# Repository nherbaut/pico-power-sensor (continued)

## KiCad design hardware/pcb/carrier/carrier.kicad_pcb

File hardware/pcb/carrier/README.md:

# PicoPower carrier — rev A engineering draft

This board sockets a Pico 2 W, provides five programmable green LEDs and a microSD slot, and carries the INA229 power monitor, fed from the interposer through a four-pin JST-XH sense connector. A five-pin JST-XH connector joins the carrier to the buffered Pi interposer. The carrier has its own USB-powered supply; instrument loads remain outside DUT energy measurements.

## Electrical schematic

This is the current KiCad schematic, including the five LED branches, INA229 and sense connector, UART connector, SPI1 microSD slot and dedicated card regulator. Matching net names are electrical connections. Click the PNG to read individual pin numbers and component values.

[Open full-size schematic PNG](schematic.png) · [Download schematic PDF](schematic.pdf).

## Front PCB layout

The sense connector and INA229 sit in a strip at the left edge, the Pico sockets in the middle, five LEDs along the right edge, and the hinged card socket in the lower-left. The UART JST-XH connector is above the microSD area. Four mounting holes provide support on a shared bench base.

[Open full-size PCB PNG](layout-front.png) · [Original front SVG](layout-front.svg).

## Review files

- [KiCad project](carrier.kicad_pro), [schematic](carrier.kicad_sch) and [routed PCB](carrier.kicad_pcb).
- [Schematic PDF](schematic.pdf), [front copper](layout-front.svg) and [back copper](layout-back.svg), viewed from above.
- [Mounting drawing](mounting.svg), [pinout](pinout.csv), [board BOM](board-bom.csv) and [circuit source](circuit.json).
- [Portable review archive](carrier-review.zip), including the local symbol and footprint libraries.
- [ERC](checks/erc.rpt), [DRC and schematic parity](checks/drc.rpt), and [source/PCB checks](checks/source-check.json).
- [PNG export provenance](images.json): source CAD hashes and image dimensions.

Open `carrier.kicad_pro` in KiCad 9. The schematic uses named nets: matching names are electrical connections. LED polarity is explicitly labelled A/K. `J_PICO` uses a combined socketed-Pico footprint; fit two 1x20 female strips at 17.78 mm row separation, with a compatible headered Pico. Its module/header height requires physical review.

`make carrier-build` deliberately overwrites carrier CAD and routes it again. Save interactive edits before using it. `make carrier-check`, `make carrier-erc` and `make carrier-drc` check the source/PCB mapping and native CAD. `make carrier-export` requires all checks to pass before exporting the review archive. Existing interposer build targets remain independent. These commands need KiCad 9, the distribution Python `pcbnew` module and NumPy.

## Electrical and mechanical choices

LED1-LED5 use GP27, GP26, GP22, GP21 and GP20 (physical pins 32, 31, 29, 27, 26), each with a 1 kOhm series resistor and a 100 kOhm GPIO pull-down. High turns an LED on; low turns it off. Firmware functions and PWM remain programmable. The [LED datasheet](https://www.kingbrightusa.com/images/catalog/spec/apt2012lzgck.pdf) gives typical Vf 2.65 V at 2 mA; using this voltage gives a 0.65 mA reference estimate per LED, not a solved operating point. Actual current and brightness remain bench checks. See the [current calculations](../../../docs/pico-carrier.md).

`J_UART` is JST B5B-XH-A(LF)(SN), with pins 1-5: GND, PICO_RX, PICO_TX, PICO_MARK, PICO_3V3. A straight-through five-wire harness uses XHP-5 housings at both ends and ten SXH-001T-P0.6 contacts. Pin 5 supplies the interposer buffer from the Pico. See the [wiring procedure](../../../docs/wiring.md).

`J_SENSE` is JST B4B-XH-A(LF)(SN), pins 1-4: SENSE_PLUS, SENSE_MINUS, SENSE_VBUS, GND, joined to interposer J3 with a straight-through XHP-4 cable. `U_PM` is the INA229AIDGSR (VSSOP-10): SPI0 on GP4-GP7 (physical 6, 7, 9, 10), ALERT on GP3, 100 nF bypass `C_PM`, a 100 kOhm CS pull-up and a 10 kOhm ALERT pull-up, all to PICO_3V3. Pin numbering follows TI SLYS023A table 5-1. The footprint is the KiCad VSSOP-10 snapshot; it has not yet been compared with TI's DGS0010A land pattern. The sense pair is fanned out from the 0.5 mm pins to J_SENSE; its Kelvin routing needs review.

J_SD uses a hinged Würth 693072010801 socket on SPI1 (GP12-GP15), separate from INA229 SPI0 (GP4-GP7). Five 10 kOhm pull-ups bias CMD/DAT0-DAT3. A TLV75533PDBVR supplies SD_3V3 from Pico USB VBUS, enabled by PICO_3V3, with 4.7 uF input/output capacitors and 22 uF/100 nF near the slot. The rails are not joined. The socket has no card-detect switch; recording requires future buffered logger firmware. See the [storage and power details](../../../docs/pico-carrier.md).

The board is 78 x 54 mm, 1.6 mm FR4, with two 35 um copper layers. Four 2.7 mm NPTH mounting holes at (4,4), (74,4), (4,50), (74,50) mm have 6 mm copper keepouts. Use M2.5 nylon hardware on a shared bench base and match board height without stressing connectors. The antenna has a copper keepout on both sides; keep base material, metal hardware and cables clear of the antenna region.

## Rebuilding the board

`make carrier-build` (generate, then the grid router) does **not currently reproduce this board**. On 2026-10-14, after the INA229 change, four regeneration attempts failed inside the router with "No route for ..." on different nets, including attempts in a scratch directory and with fixed hash seeds; the cause was not identified. The saved `carrier.kicad_pcb` (routed, with ERC, DRC and parity clean) is therefore the source of truth. Edit it in KiCad or with a targeted script that starts from the routed board, and do not run `make carrier-build` over it. A known-good copy of the routed board and its `circuit.json` is kept locally in `.build/carrier-good/`, which git ignores, so commit the board before experimenting.

## Release and physical acceptance

**Engineering draft, not fabrication-ready.** Automated reports describe CAD checks only. There are no released Gerbers, procurement actions or carrier firmware. Native footprints are snapshotted locally; the Sullins socket is a custom dimensional draft. Complete component/circuit/footprint/orientation review and physical mock-up before prototype fabrication; complete assembled-board electrical tests before DUT connection. The [CSV checklist](../../release-checklist.csv), [release procedure](../../../docs/release.md) and [current review findings](../../review/README.md) record both gates, which remain blocked.

KiCad 9.0.9 reports zero ERC violations, zero DRC violations, zero unconnected pads and zero schematic parity issues. Ten carrier regression tests cover connector mappings, LED GPIOs, separate SD power and SPI1 allocation; run them with the thirteen existing interposer tests. Re-run checks after edits; do not suppress violations to obtain a release.

With instrument and DUT supplies disabled, verify connector continuity, LED polarity and separation from DUT power. After electrical review, validate independent USB power and the INA229 3.3 V supply before attaching DUT sense wiring. Exercise all five LEDs individually, together and with PWM; check reset behavior. Validate SPI device identification first: the INA229's MANUFACTURER_ID register (address 3Eh) reads 0x5449 ("TI" in ASCII) and its DEVICE_ID register (3Fh) reads 0x2291 on the datasheet revision read, where the upper twelve bits (0x229) identify the device and the low four bits are the die revision (a different revision does not by itself mean a fake). Then validate ALERT, UART and marker signals, then card write/read checks and supply stability with SD writes, Wi-Fi and all indicators active. Measure card current peaks and regulator temperature; the 500 mA regulator rating is not a board-level continuous-load guarantee. Follow the existing interposer power-off procedure. Firmware/test tooling for these bench exercises is a separate milestone.

Record actual module revisions, socket height, supply voltages, traces, equipment and results. A Linux shutdown alone is not proof that Pi 3.3 V is off. Physical acceptance remains **not performed**.

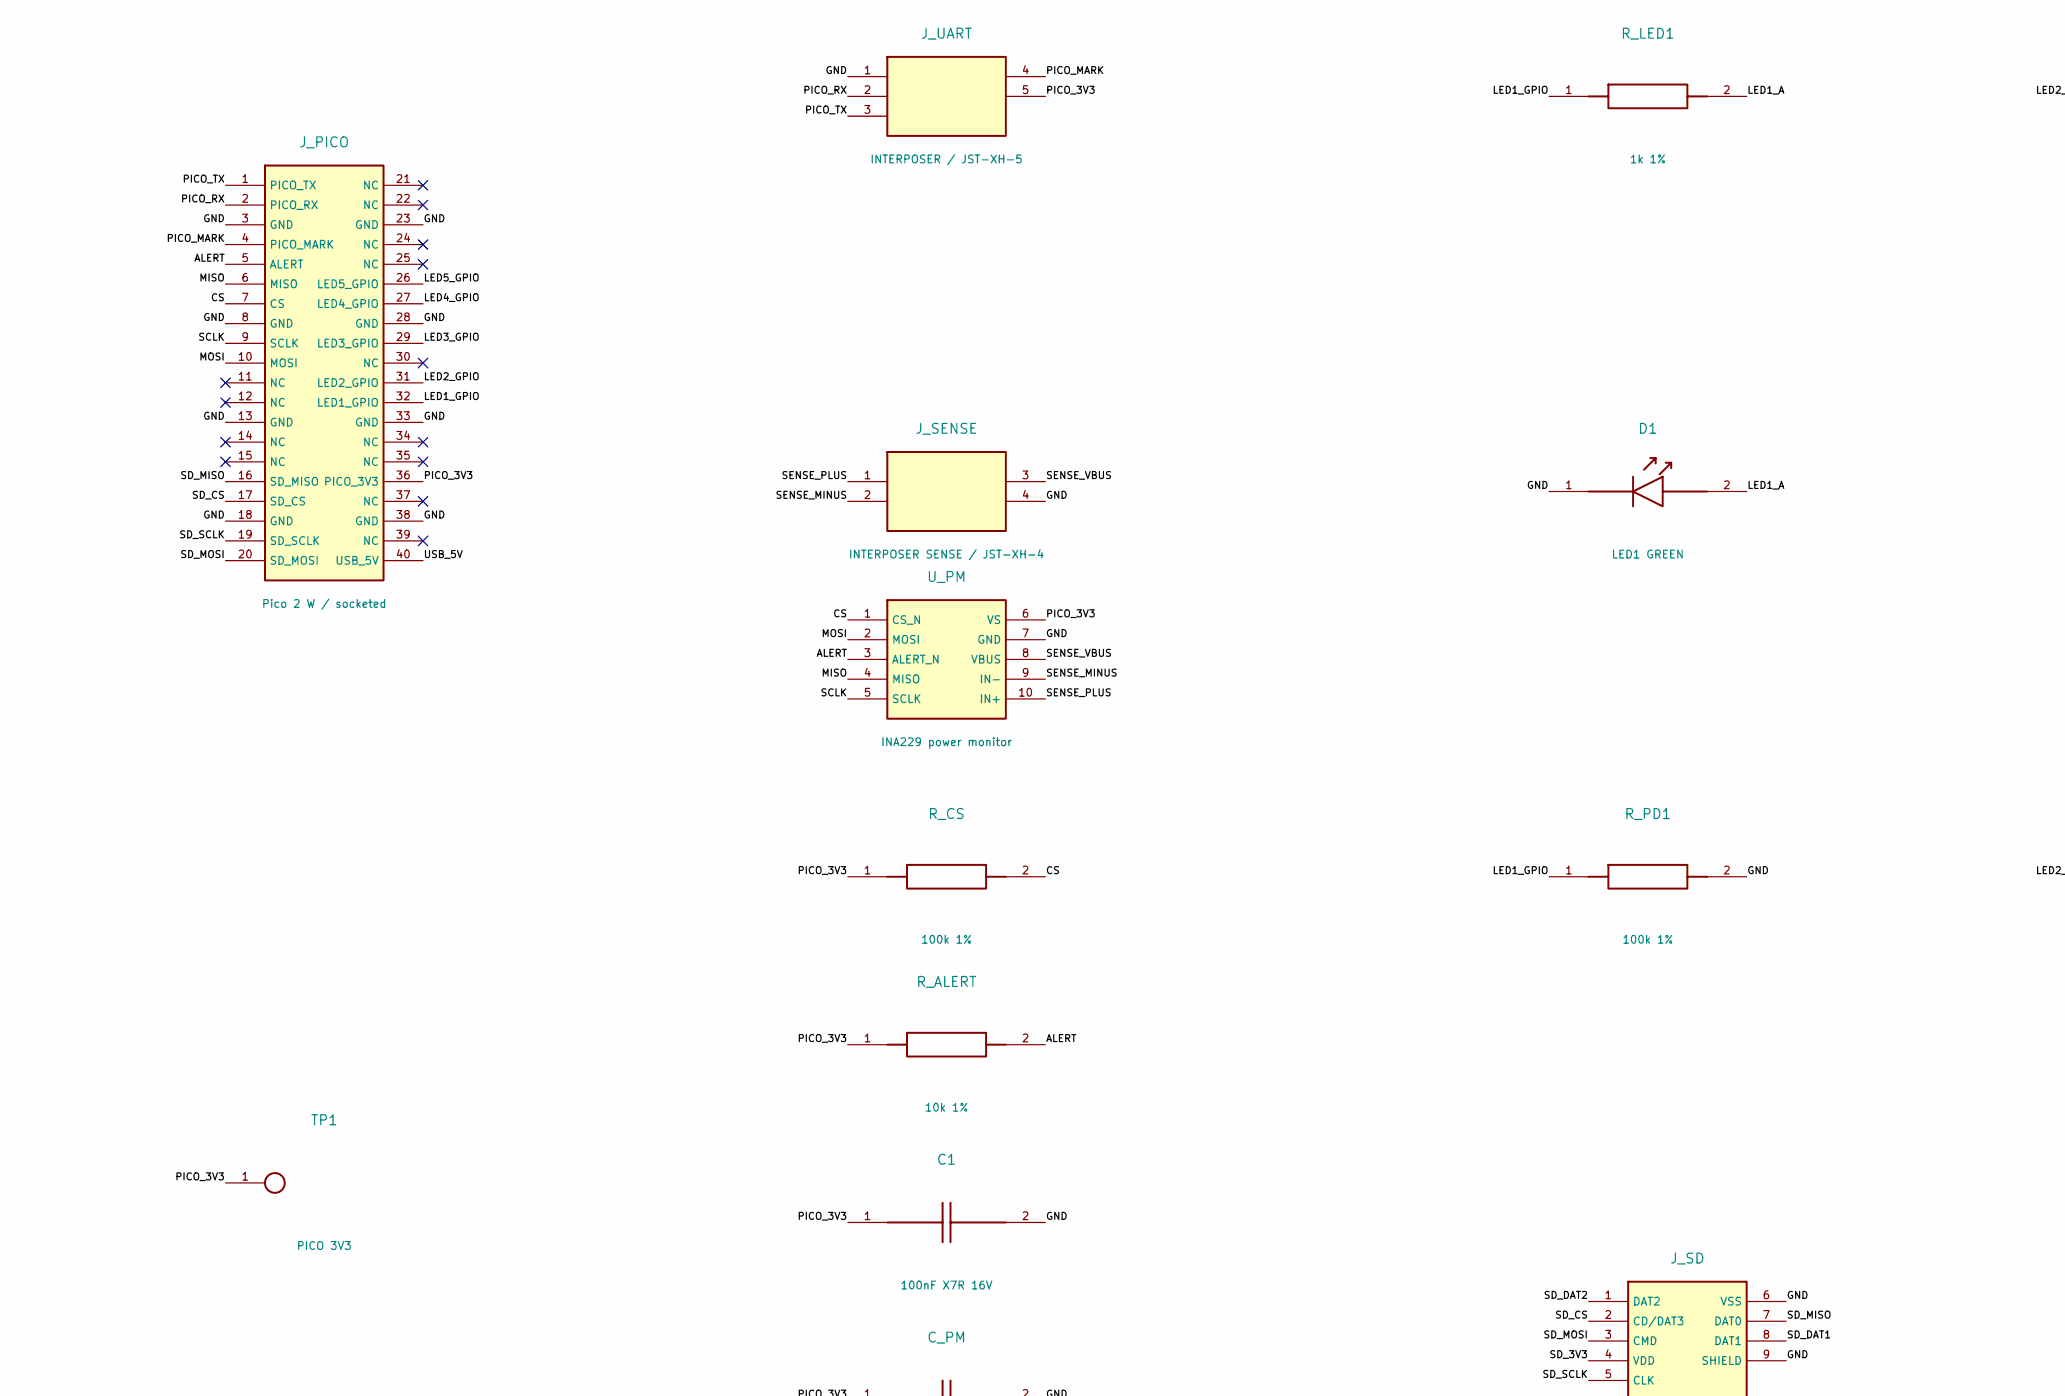
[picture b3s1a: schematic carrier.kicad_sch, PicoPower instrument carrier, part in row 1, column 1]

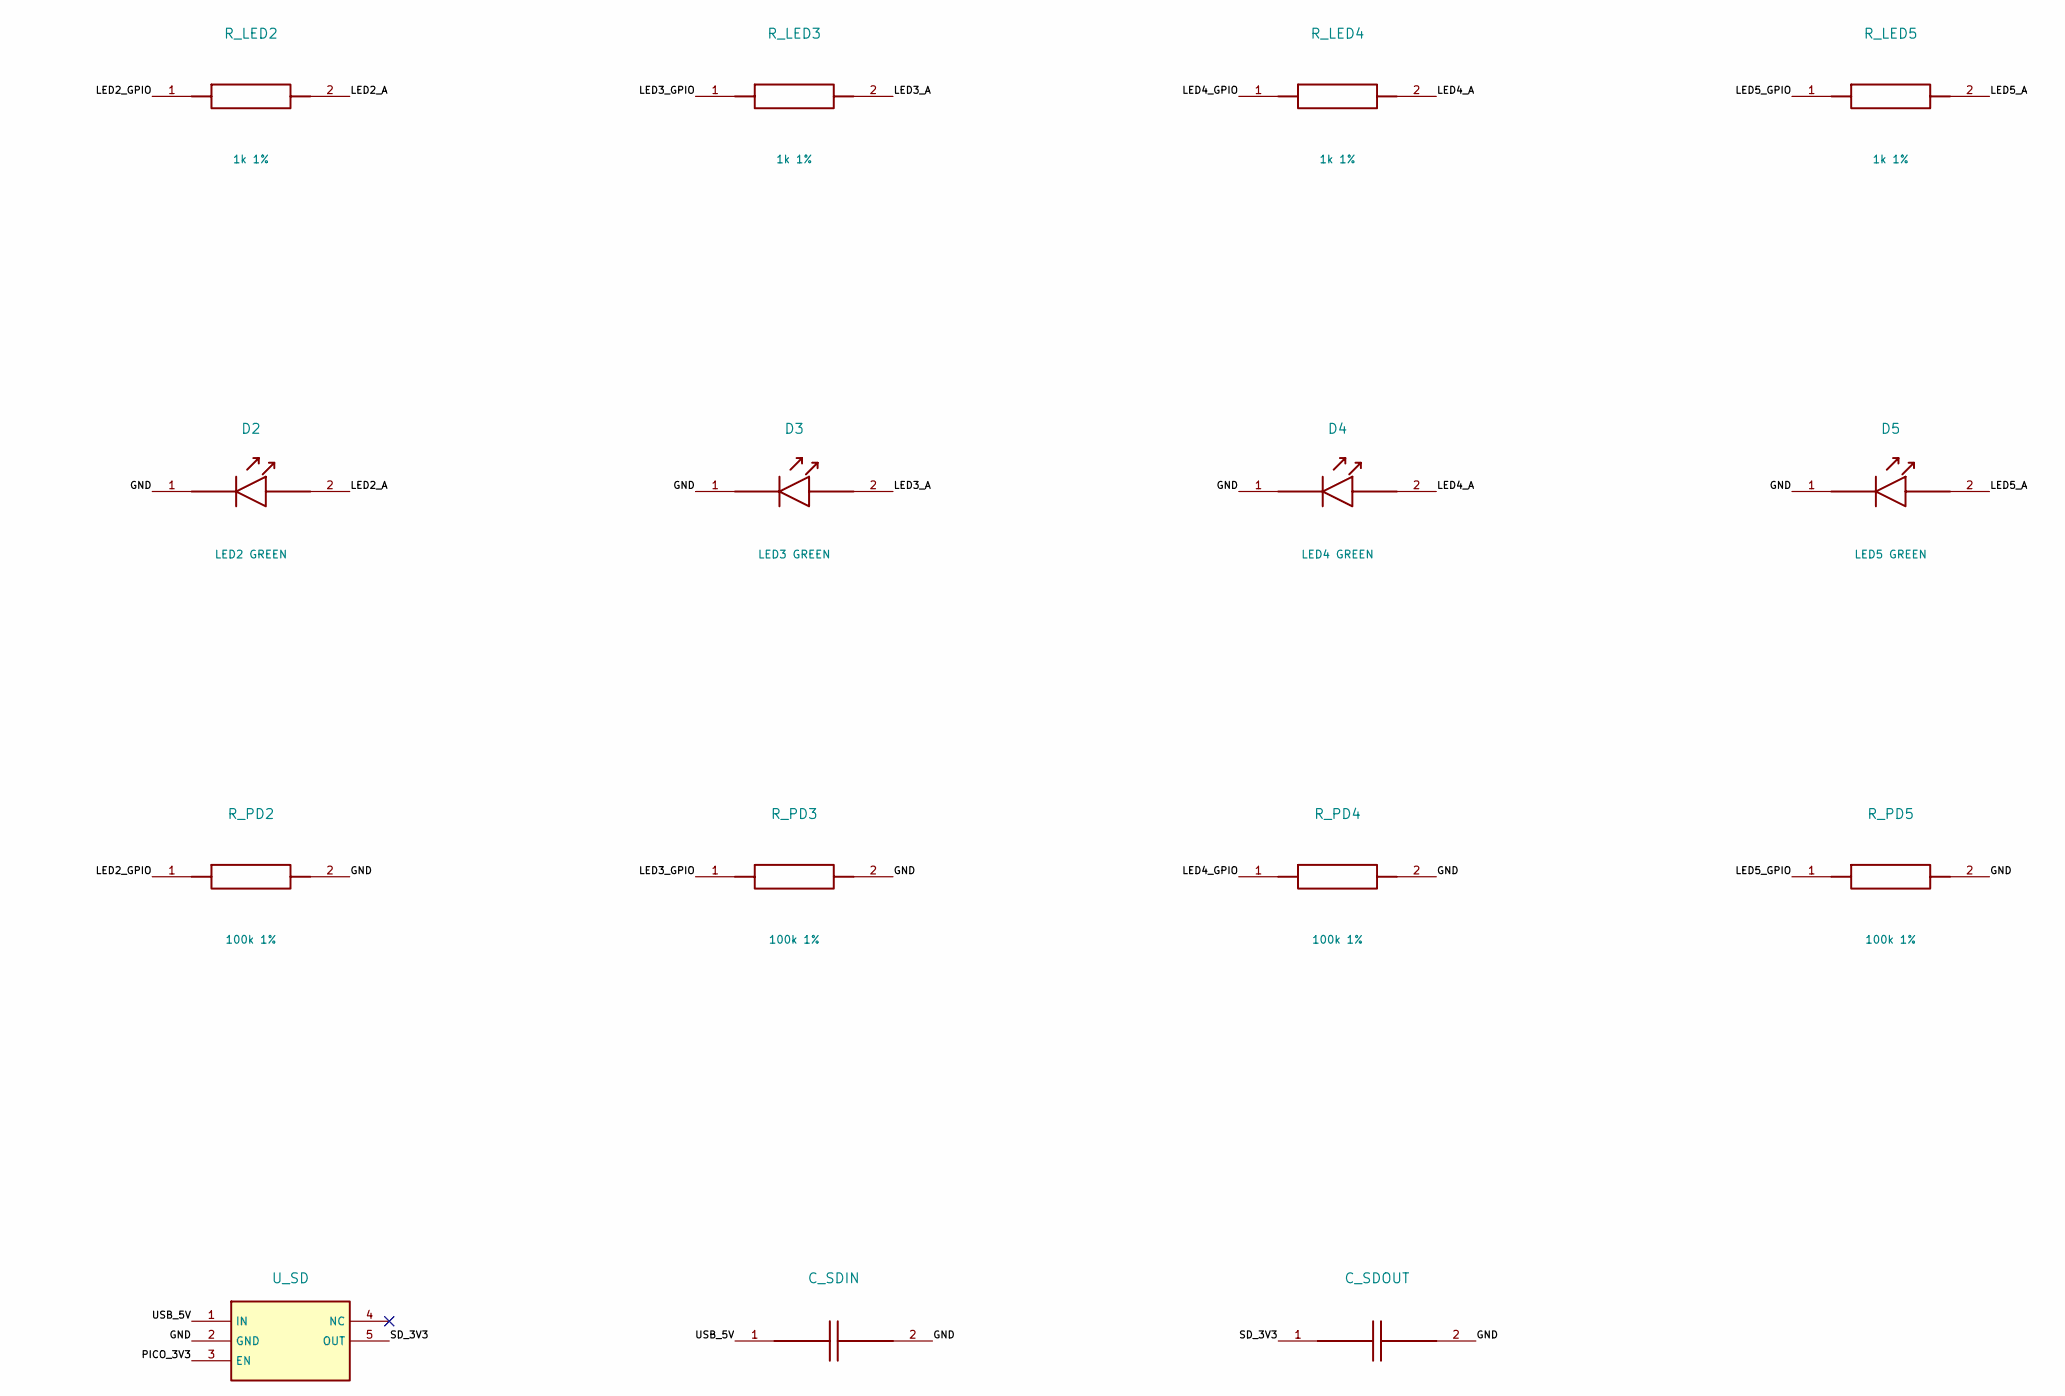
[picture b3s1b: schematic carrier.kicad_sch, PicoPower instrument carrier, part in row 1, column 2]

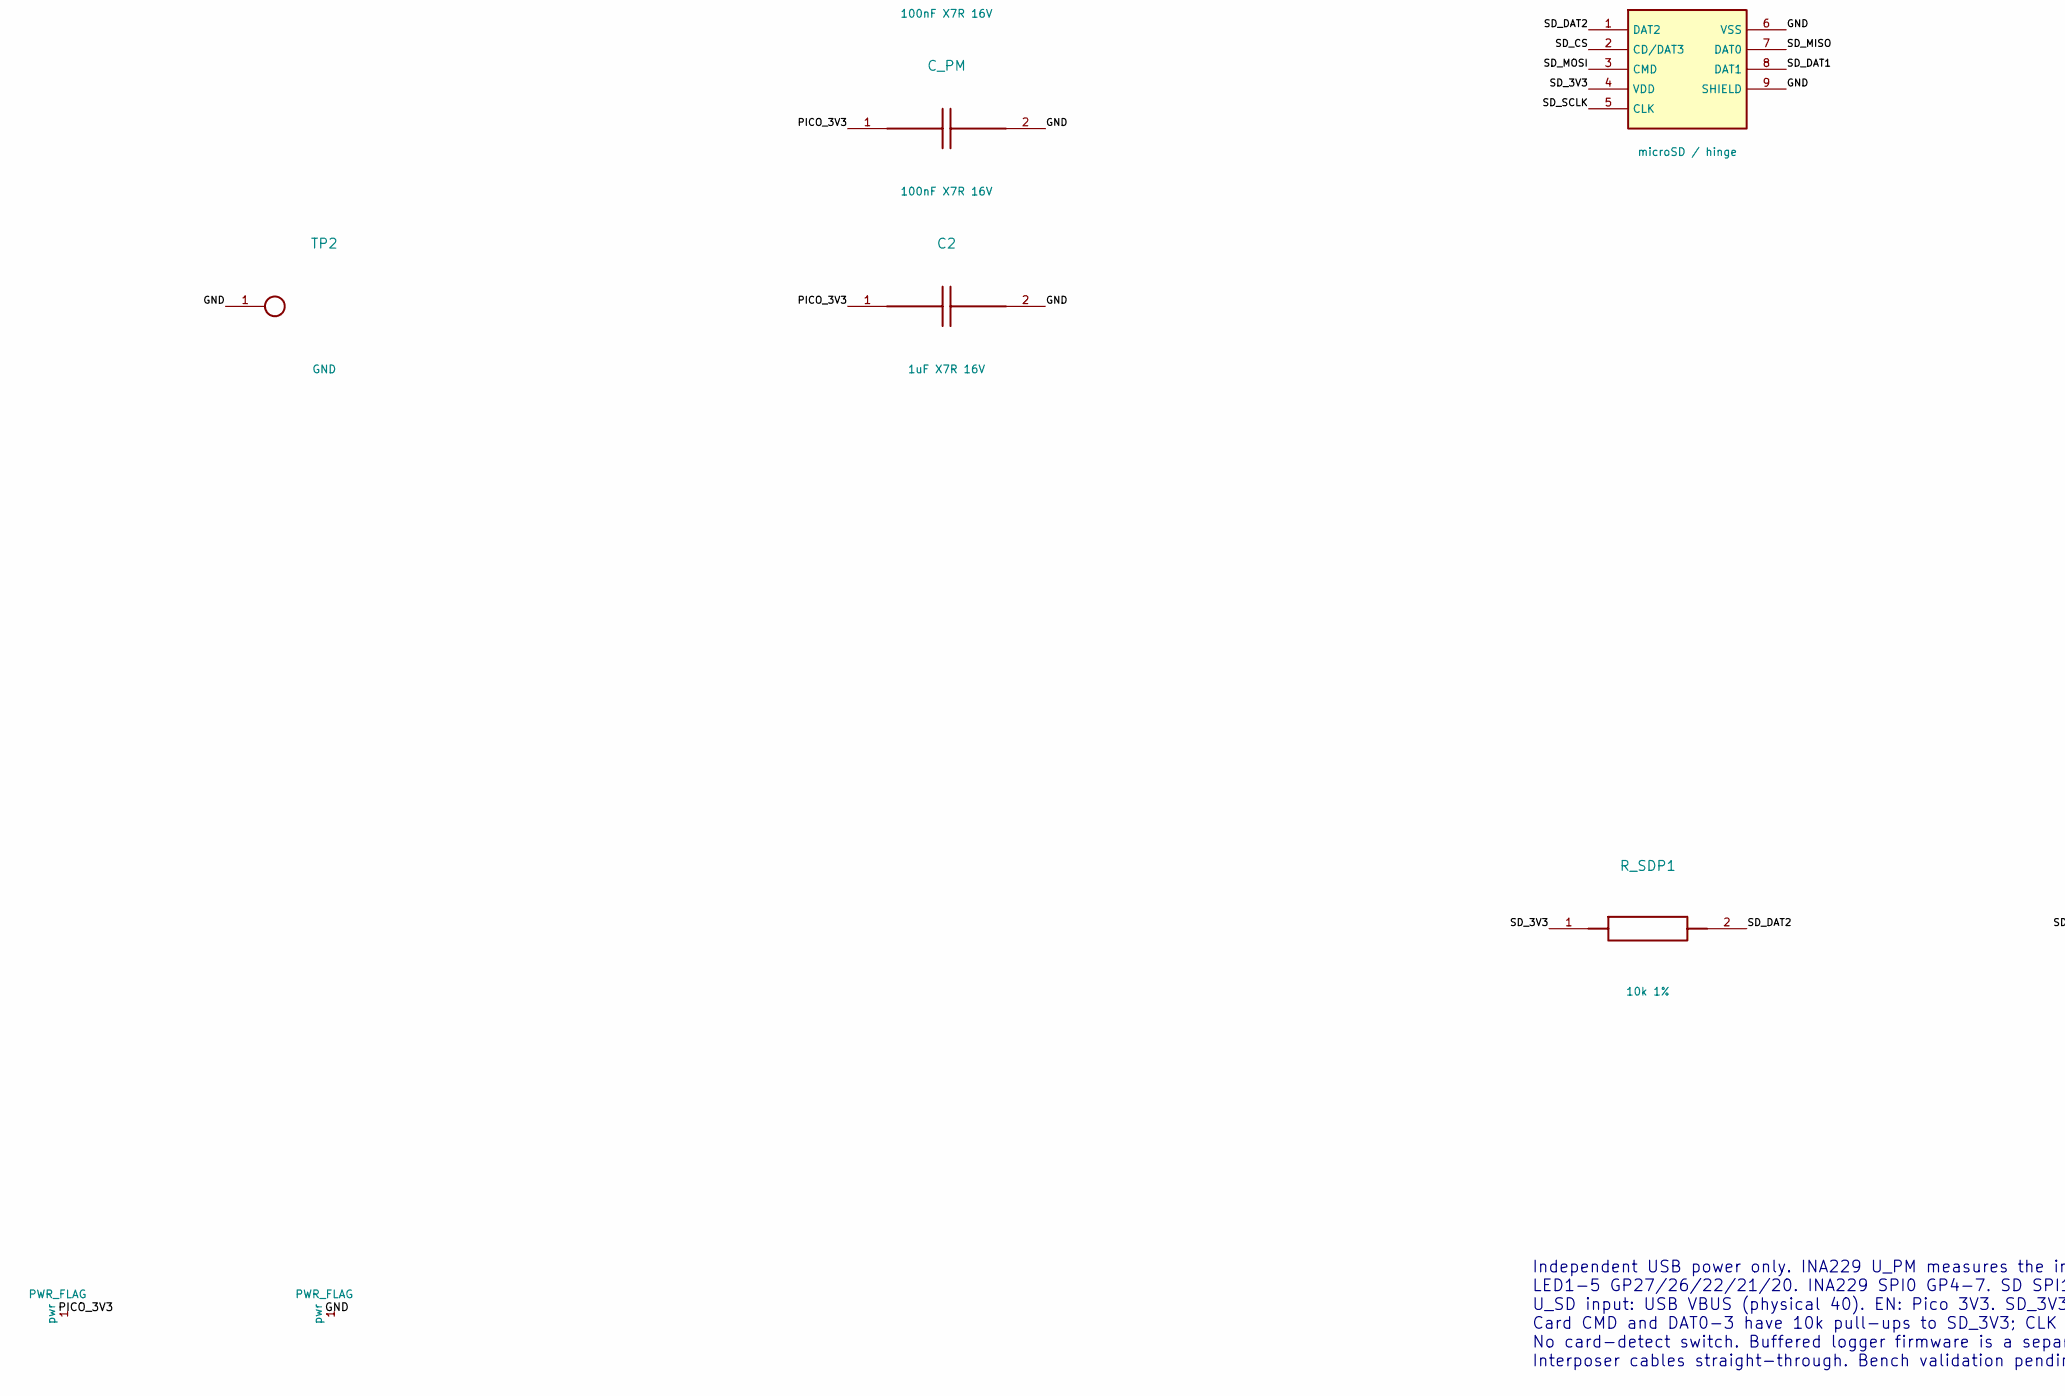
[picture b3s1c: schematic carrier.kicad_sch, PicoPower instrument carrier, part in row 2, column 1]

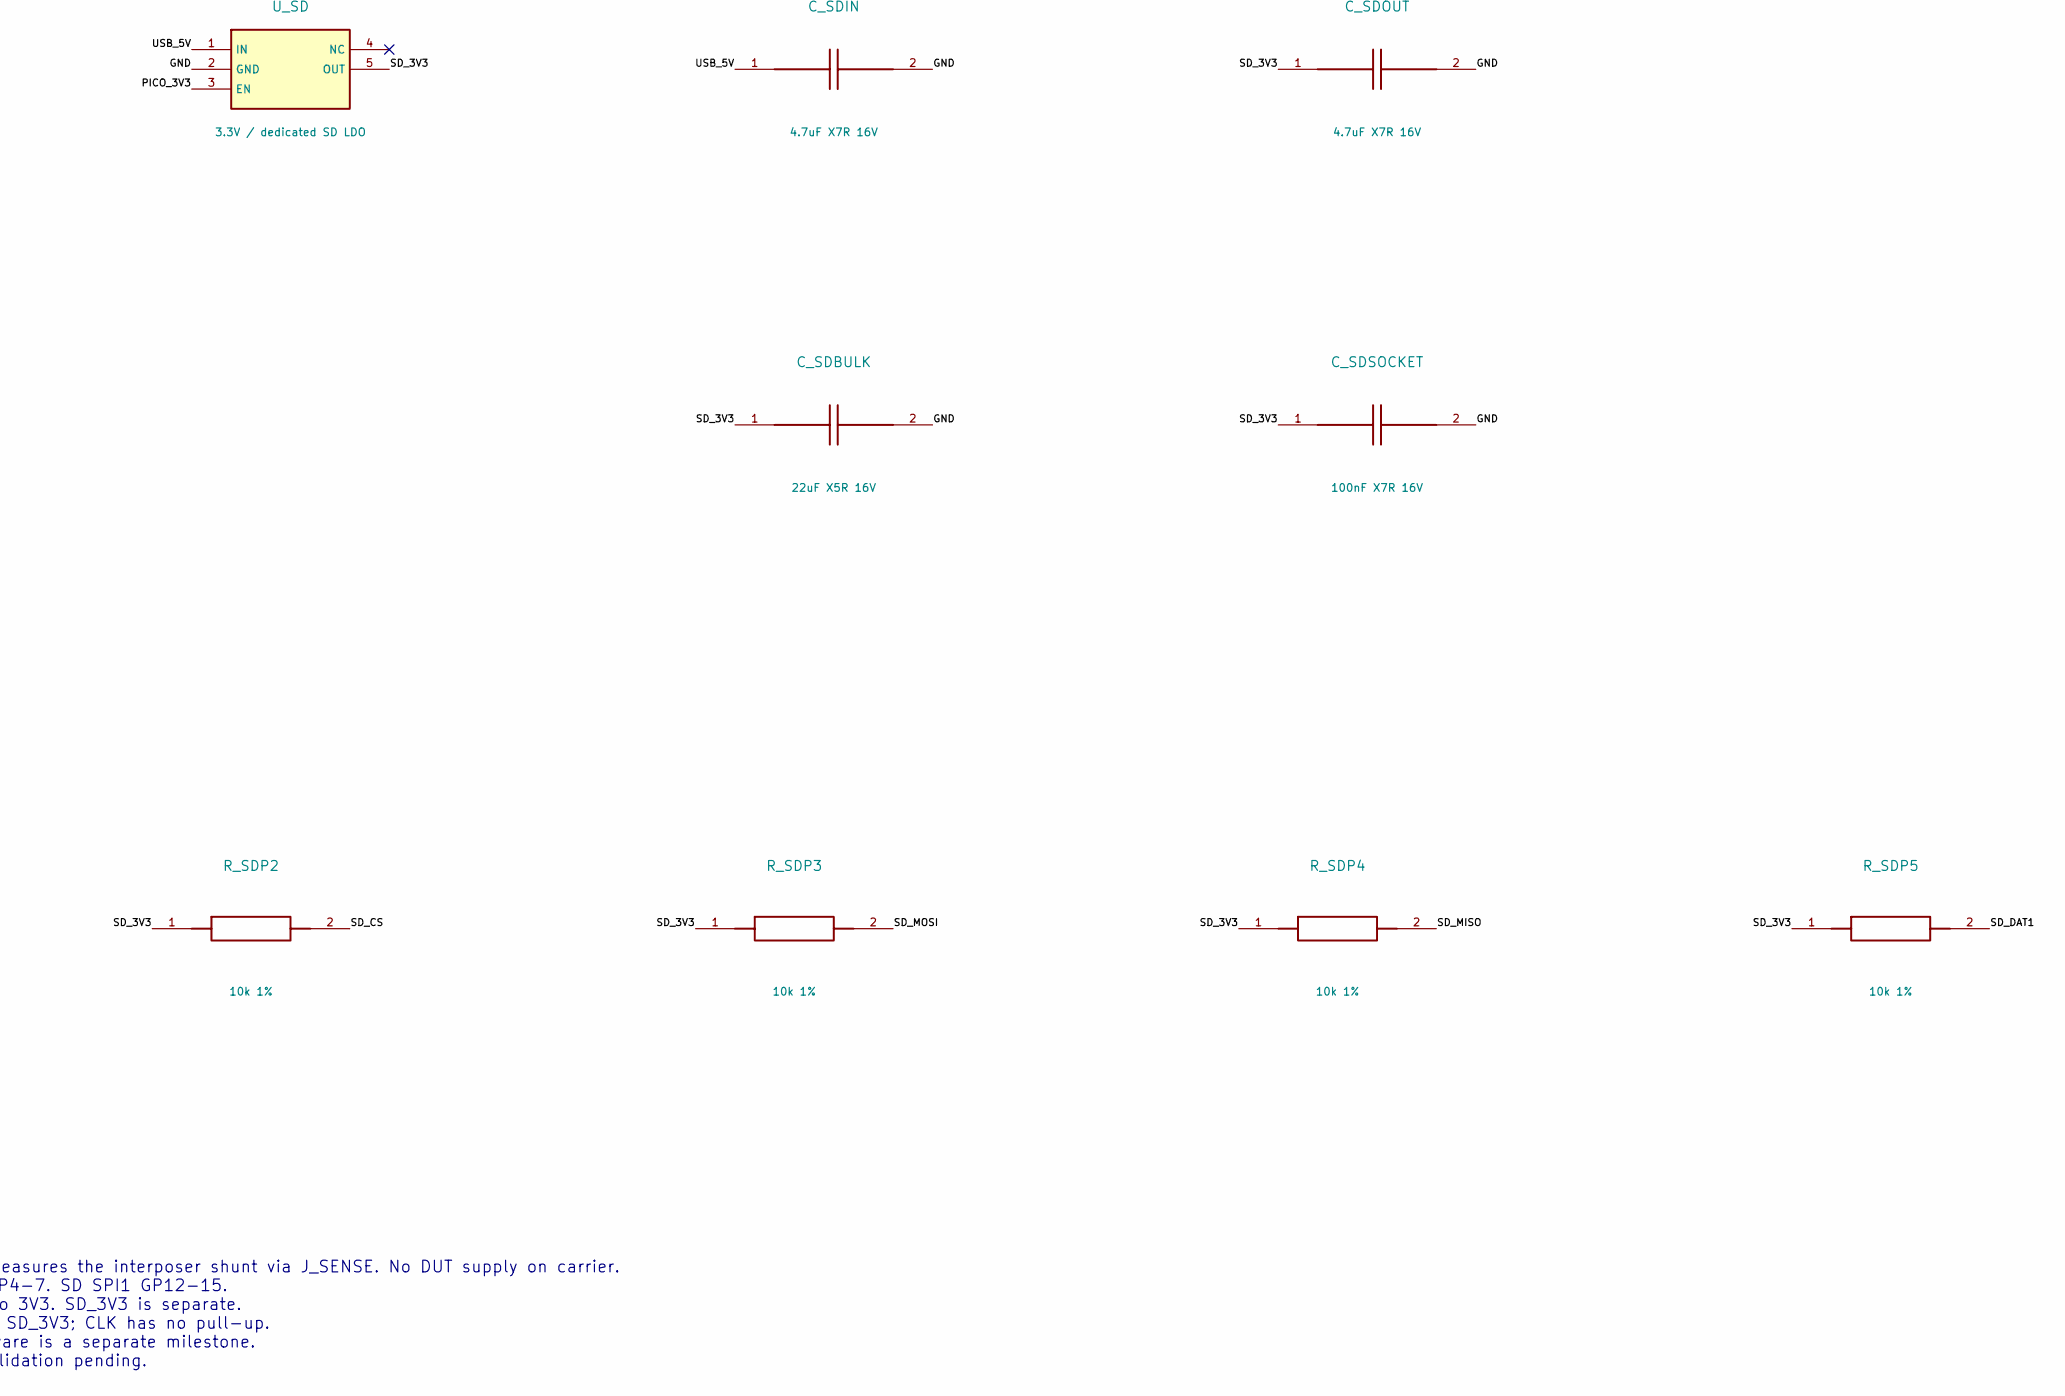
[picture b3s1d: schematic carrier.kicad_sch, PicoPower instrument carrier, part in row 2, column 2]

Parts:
C1: 100nF X7R 16V; C_0805_Murata; MPN GRM21BR71C104KA01L
C2: 1uF X7R 16V; C_0805_Murata; MPN GRM21BR71C105KA01L
C_PM: 100nF X7R 16V; C_0805_Murata; MPN GRM21BR71C104KA01L
C_SDBULK: 22uF X5R 16V; C_1206; MPN CL31A226KOHNNNE
C_SDIN: 4.7uF X7R 16V; C_0805_Murata; MPN GRM21BR71C475KA73L
C_SDOUT: 4.7uF X7R 16V; C_0805_Murata; MPN GRM21BR71C475KA73L
C_SDSOCKET: 100nF X7R 16V; C_0805_Murata; MPN GRM21BR71C104KA01L
D1: LED1 GREEN; LED_0805; MPN APT2012LZGCK
D2: LED2 GREEN; LED_0805; MPN APT2012LZGCK
D3: LED3 GREEN; LED_0805; MPN APT2012LZGCK
D4: LED4 GREEN; LED_0805; MPN APT2012LZGCK
D5: LED5 GREEN; LED_0805; MPN APT2012LZGCK
J_PICO: Pico 2 W / socketed; Pico_Socketed; MPN Pico 2 W
J_SD: microSD / hinge; microSD_Wuerth; MPN 693072010801
J_SENSE: INTERPOSER SENSE / JST-XH-4; XH4; MPN B4B-XH-A(LF)(SN)
J_UART: INTERPOSER / JST-XH-5; XH5; MPN B5B-XH-A(LF)(SN)
R_ALERT: 10k 1%; R_0805; MPN CRCW080510K0FKEA
R_CS: 100k 1%; R_0805; MPN CRCW0805100KFKEA
R_LED1, R_LED2, R_LED3, R_LED4, R_LED5: 1k 1%; R_0805; MPN CRCW08051K00FKEA
R_PD1, R_PD2, R_PD3, R_PD4, R_PD5: 100k 1%; R_0805; MPN CRCW0805100KFKEA
R_SDP1, R_SDP2, R_SDP3, R_SDP4, R_SDP5: 10k 1%; R_0805; MPN CRCW080510K0FKEA
TP1: PICO 3V3; TestPoint
TP2: GND; TestPoint
U_PM: INA229 power monitor; VSSOP10; MPN INA229AIDGSR
U_SD: 3.3V / dedicated SD LDO; SOT23_5; MPN TLV75533PDBVR

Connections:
/ALERT: J_PICO.5 (ALERT), R_ALERT.2 (ALERT), U_PM.3 (ALERT_N)
/CS: J_PICO.7 (CS), R_CS.2 (CS), U_PM.1 (CS_N)
/GND: C1.2 (GND), C2.2 (GND), C_PM.2 (GND), C_SDBULK.2 (GND), C_SDIN.2 (GND), C_SDOUT.2 (GND), C_SDSOCKET.2 (GND), D1.1 (K), D2.1 (K), D3.1 (K), D4.1 (K), D5.1 (K), J_PICO.3 (GND), J_PICO.8 (GND), J_PICO.13 (GND), J_PICO.18 (GND), J_PICO.23 (GND), J_PICO.28 (GND), J_PICO.33 (GND), J_PICO.38 (GND), J_SD.6 (VSS), J_SD.9 (SHIELD), J_SENSE.4 (GND), J_UART.1 (GND), R_PD1.2 (GND), R_PD2.2 (GND), R_PD3.2 (GND), R_PD4.2 (GND), R_PD5.2 (GND), TP2.1, U_PM.7 (GND), U_SD.2 (GND)
/LED1_A: D1.2 (A), R_LED1.2 (LED1_A)
/LED1_GPIO: J_PICO.32 (LED1_GPIO), R_LED1.1 (LED1_GPIO), R_PD1.1 (LED1_GPIO)
/LED2_A: D2.2 (A), R_LED2.2 (LED2_A)
/LED2_GPIO: J_PICO.31 (LED2_GPIO), R_LED2.1 (LED2_GPIO), R_PD2.1 (LED2_GPIO)
/LED3_A: D3.2 (A), R_LED3.2 (LED3_A)
/LED3_GPIO: J_PICO.29 (LED3_GPIO), R_LED3.1 (LED3_GPIO), R_PD3.1 (LED3_GPIO)
/LED4_A: D4.2 (A), R_LED4.2 (LED4_A)
/LED4_GPIO: J_PICO.27 (LED4_GPIO), R_LED4.1 (LED4_GPIO), R_PD4.1 (LED4_GPIO)
/LED5_A: D5.2 (A), R_LED5.2 (LED5_A)
/LED5_GPIO: J_PICO.26 (LED5_GPIO), R_LED5.1 (LED5_GPIO), R_PD5.1 (LED5_GPIO)
/MISO: J_PICO.6 (MISO), U_PM.4 (MISO)
/MOSI: J_PICO.10 (MOSI), U_PM.2 (MOSI)
/PICO_3V3: C1.1 (PICO_3V3), C2.1 (PICO_3V3), C_PM.1 (PICO_3V3), J_PICO.36 (PICO_3V3), J_UART.5 (PICO_3V3), R_ALERT.1 (PICO_3V3), R_CS.1 (PICO_3V3), TP1.1, U_PM.6 (VS), U_SD.3 (EN)
/PICO_MARK: J_PICO.4 (PICO_MARK), J_UART.4 (PICO_MARK)
/PICO_RX: J_PICO.2 (PICO_RX), J_UART.2 (PICO_RX)
/PICO_TX: J_PICO.1 (PICO_TX), J_UART.3 (PICO_TX)
/SCLK: J_PICO.9 (SCLK), U_PM.5 (SCLK)
/SD_3V3: C_SDBULK.1 (SD_3V3), C_SDOUT.1 (SD_3V3), C_SDSOCKET.1 (SD_3V3), J_SD.4 (VDD), R_SDP1.1 (SD_3V3), R_SDP2.1 (SD_3V3), R_SDP3.1 (SD_3V3), R_SDP4.1 (SD_3V3), R_SDP5.1 (SD_3V3), U_SD.5 (OUT)
/SD_CS: J_PICO.17 (SD_CS), J_SD.2 (CD/DAT3), R_SDP2.2 (SD_CS)
/SD_DAT1: J_SD.8 (DAT1), R_SDP5.2 (SD_DAT1)
/SD_DAT2: J_SD.1 (DAT2), R_SDP1.2 (SD_DAT2)
/SD_MISO: J_PICO.16 (SD_MISO), J_SD.7 (DAT0), R_SDP4.2 (SD_MISO)
/SD_MOSI: J_PICO.20 (SD_MOSI), J_SD.3 (CMD), R_SDP3.2 (SD_MOSI)
/SD_SCLK: J_PICO.19 (SD_SCLK), J_SD.5 (CLK)
/SENSE_MINUS: J_SENSE.2 (SENSE_MINUS), U_PM.9 (IN-)
/SENSE_PLUS: J_SENSE.1 (SENSE_PLUS), U_PM.10 (IN+)
/SENSE_VBUS: J_SENSE.3 (SENSE_VBUS), U_PM.8 (VBUS)
/USB_5V: C_SDIN.1 (USB_5V), J_PICO.40 (USB_5V), U_SD.1 (IN)

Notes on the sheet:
Independent USB power only. INA229 U_PM measures the interposer shunt via J_SENSE. No DUT supply on carrier. LED1-5 GP27/26/22/21/20. INA229 SPI0 GP4-7. SD SPI1 GP12-15. U_SD input: USB VBUS (physical 40). EN: Pico 3V3. SD_3V3 is separate. Card CMD and DAT0-3 have 10k pull-ups to SD_3V3; CLK has no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

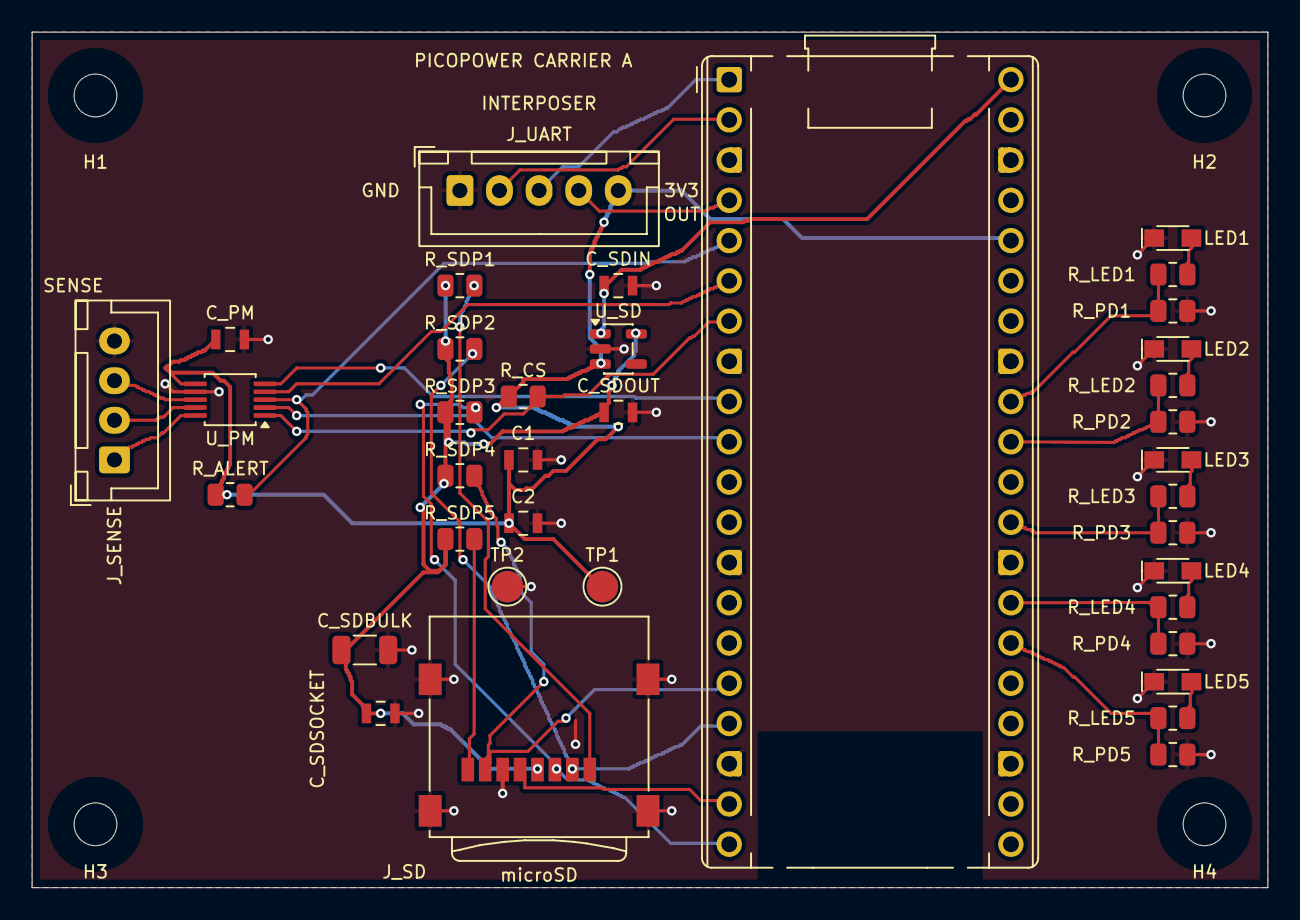
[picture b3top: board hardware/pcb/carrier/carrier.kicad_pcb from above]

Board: 2 copper layers, 78.0 x 54.0 mm, 41 parts (0 on the bottom side), 31 nets.

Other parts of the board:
H1, H2, H3, H4: MountingHole_2.7mm_M2.5
